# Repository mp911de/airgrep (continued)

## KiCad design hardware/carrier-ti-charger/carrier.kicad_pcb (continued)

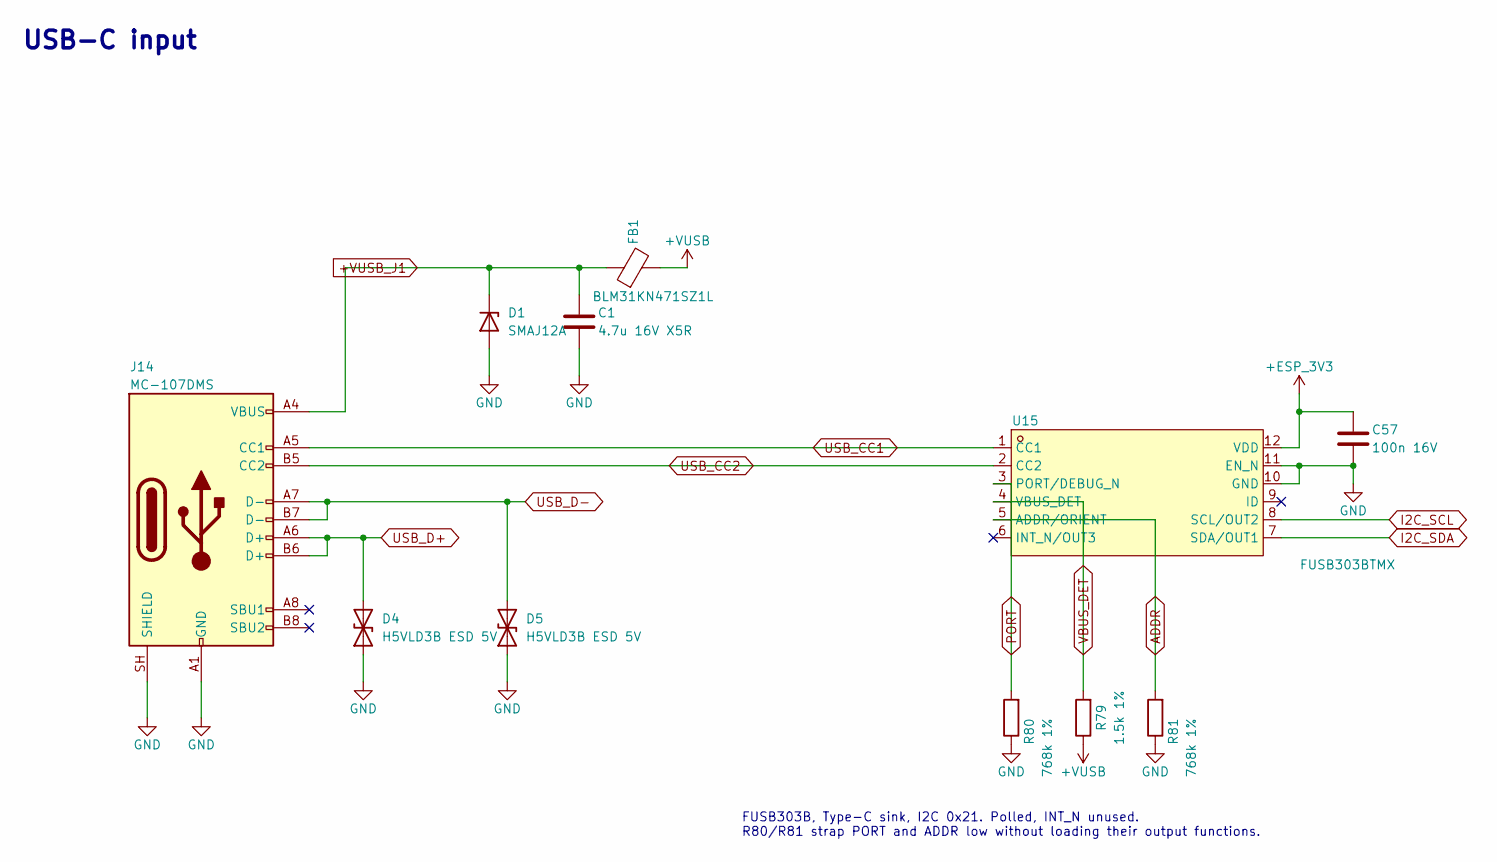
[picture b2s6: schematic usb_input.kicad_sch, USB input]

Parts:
C1: 4.7u 16V X5R; C_0603_1608Metric; LCSC C19666
C57: 100n 16V; C_0402_1005Metric_NoSilk; MPN CL05B104KO5NNNC; LCSC C1525
D1: SMAJ12A; D_SMA; LCSC C19077531
D4, D5: H5VLD3B ESD 5V; D_SOD-323; MPN H5VLD3B; LCSC C20615805
FB1: BLM31KN471SZ1L; L_1206_3216Metric; LCSC C710518
J14: MC-107DMS; USB_C_Receptacle_Hanbo_MC-107DMS; LCSC C3039295
R79: 1.5k 1%; R_0402_1005Metric_NoSilk; MPN 0402WGF1501TCE; LCSC C25867
R80, R81: 768k 1%; R_0402_1005Metric_NoSilk; MPN FRC0402F7683TS; LCSC C49196905
U15: FUSB303BTMX; X2QFN-12_L1.6-W1.6-P0.40-TL; LCSC C895444

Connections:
+ESP_3V3: C57.1, U15.12 (VDD); also elsewhere on the board
+VUSB: FB1.2, R79.1; also elsewhere on the board
+VUSB_J1: C1.1, D1.1 (K), FB1.1, J14.A4 (VBUS), J14.A9 (VBUS), J14.B4 (VBUS), J14.B9 (VBUS)
ADDR: R81.2, U15.5 (ADDR/ORIENT)
GND: C1.2, C57.2, D1.2 (A), D4.1 (A1), D5.1 (A1), J14.A1 (GND), J14.A12 (GND), J14.B1 (GND), J14.B12 (GND), J14.SH (SHIELD), R80.1, R81.1, U15.10 (GND), U15.11 (EN_N); also elsewhere on the board
I2C_SCL: U15.8 (SCL/OUT2); also elsewhere on the board
I2C_SDA: U15.7 (SDA/OUT1); also elsewhere on the board
PORT: R80.2, U15.3 (PORT/DEBUG_N)
USB_CC1: J14.A5 (CC1), U15.1 (CC1)
USB_CC2: J14.B5 (CC2), U15.2 (CC2)
USB_D+: D4.2 (A2), J14.A6 (D+), J14.B6 (D+); also elsewhere on the board
USB_D-: D5.2 (A2), J14.A7 (D-), J14.B7 (D-); also elsewhere on the board
VBUS_DET: R79.2, U15.4 (VBUS_DET)

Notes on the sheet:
USB-C input
FUSB303B, Type-C sink, I2C 0x21. Polled, INT_N unused. R80/R81 strap PORT and ADDR low without loading their output functions.

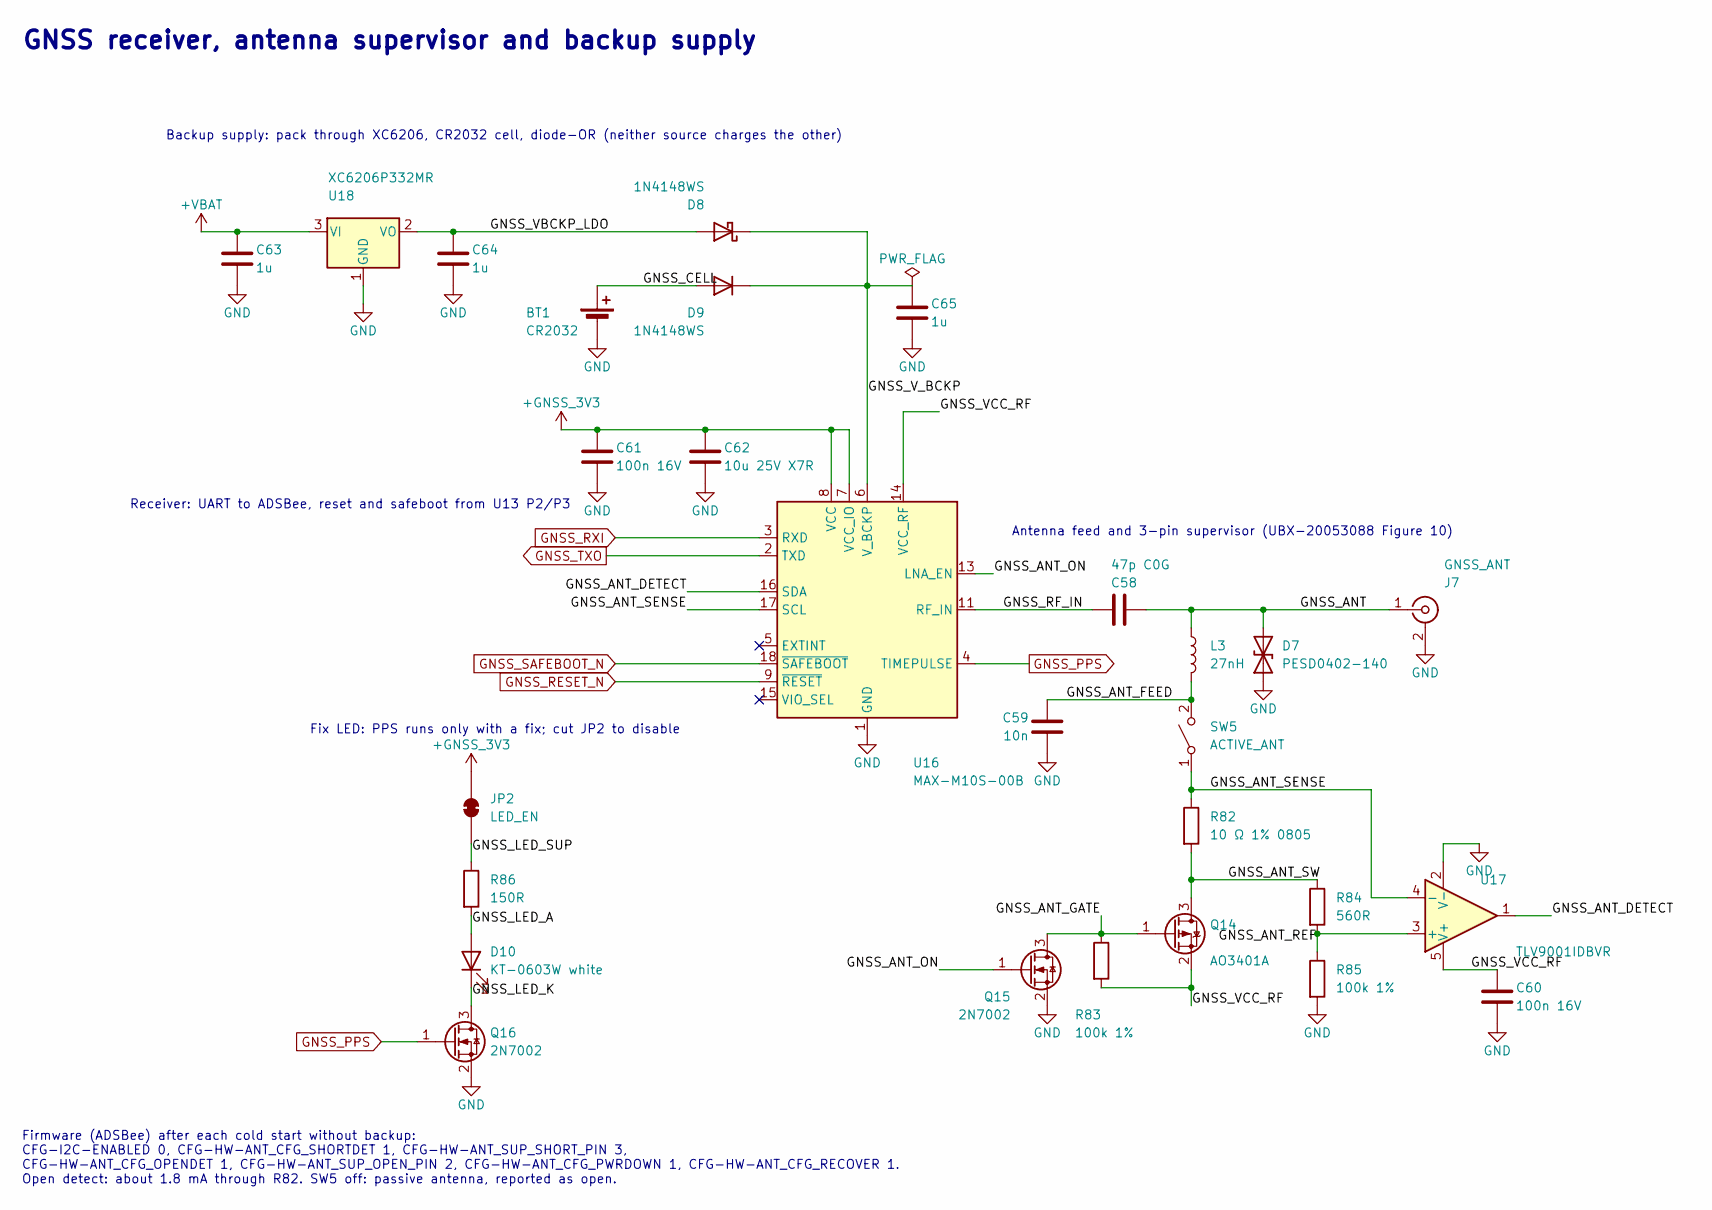
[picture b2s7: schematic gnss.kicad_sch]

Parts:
BT1: CR2032; BAT-SMD_BS-CR2032-8; MPN BS-CR2032-8; LCSC C7498149
C58: 47p C0G; C_0402_1005Metric_NoSilk; MPN 0402CG470J500NT; LCSC C1567
C59: 10n; C_0603_1608Metric; LCSC C57112
C60, C61: 100n 16V; C_0402_1005Metric_NoSilk; MPN CL05B104KO5NNNC; LCSC C1525
C62: 10u 25V X7R; C_0805_2012Metric; MPN CL21B106KAYQNNE; LCSC C3039694
C63, C64, C65: 1u; C_0603_1608Metric; MPN CL10A105KB8NNNC; LCSC C15849
D7: PESD0402-140; D_0402_1005Metric; MPN PESD0402-140; LCSC C10662
D8, D9: 1N4148WS; D_SOD-323; MPN 1N4148WS; LCSC C2128
D10: KT-0603W white; LED_0603_1608Metric; MPN KT-0603W; LCSC C2290
J7: GNSS_ANT; U.FL_Hirose_U.FL-R-SMT-1_Vertical; MPN U.FL-R-SMT-1(80); LCSC C88374
JP2: LED_EN; SolderJumper-2_P1.3mm_Bridged_RoundedPad1.0x1.5mm
L3: 27nH; L_0402_1005Metric; MPN LQG15HS27NJ02D; LCSC C12669
Q14: AO3401A; SOT-23; MPN AO3401A; LCSC C15127
Q15, Q16: 2N7002; SOT-23; MPN 2N7002; LCSC C8545
R82: 10 Ω 1% 0805; R_0805_2012Metric_NoSilk; LCSC C17415
R83, R85: 100k 1%; R_0603_1608Metric; LCSC C25803
R84: 560R; R_0603_1608Metric; MPN 0603WAF5600T5E; LCSC C23204
R86: 150R; R_0603_1608Metric; LCSC C22808
SW5: ACTIVE_ANT; SW-SMD_SHOUHAN_2.54-1P_TPGT; MPN 2.54-1P TPGT; LCSC C7421519
U16: MAX-M10S-00B; ublox_MAX-M10S; MPN MAX-M10S-00B; LCSC C4153167
U17: TLV9001IDBVR; SOT-23-5; MPN TLV9001IDBVR; LCSC C398363
U18: XC6206P332MR; SOT-23; MPN XC6206P332MR; LCSC C5446

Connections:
+GNSS_3V3: C61.1, C62.1, JP2.2 (B), U16.7 (VCC_IO), U16.8 (VCC); also elsewhere on the board
+VBAT: C63.1, U18.3 (VI); also elsewhere on the board
/GNSS/GNSS_ANT: C58.2, D7.2 (A2), J7.1 (In), L3.1
/GNSS/GNSS_ANT_DETECT: U16.16 (SDA), U17.1
/GNSS/GNSS_ANT_FEED: C59.1, L3.2, SW5.2 (B)
/GNSS/GNSS_ANT_GATE: Q14.1 (G), Q15.3 (D), R83.1
/GNSS/GNSS_ANT_ON: Q15.1 (G), U16.13 (LNA_EN)
/GNSS/GNSS_ANT_REF: R84.2, R85.1, U17.3 (+)
/GNSS/GNSS_ANT_SENSE: R82.1, SW5.1 (A), U16.17 (SCL), U17.4 (-)
/GNSS/GNSS_ANT_SW: Q14.3 (D), R82.2, R84.1
/GNSS/GNSS_CELL: BT1.1 (+), D9.2 (A)
/GNSS/GNSS_LED_A: D10.2 (A), R86.2
/GNSS/GNSS_LED_K: D10.1 (K), Q16.3 (D)
/GNSS/GNSS_LED_SUP: JP2.1 (A), R86.1
/GNSS/GNSS_RF_IN: C58.1, U16.11 (RF_IN)
/GNSS/GNSS_VBCKP_LDO: C64.1, D8.2 (A), U18.2 (VO)
/GNSS/GNSS_VCC_RF: C60.1, Q14.2 (S), R83.2, U16.14 (VCC_RF), U17.5 (V+)
/GNSS/GNSS_V_BCKP: C65.1, D8.1 (K), D9.1 (K), U16.6 (V_BCKP)
GND: BT1.2 (-), C59.2, C60.2, C61.2, C62.2, C63.2, C64.2, C65.2, D7.1 (A1), J7.2 (Ext), Q15.2 (S), Q16.2 (S), R85.2, U16.1 (GND), U16.10 (GND), U16.12 (GND), U17.2 (V-), U18.1 (GND); also elsewhere on the board
GNSS_PPS: Q16.1 (G), U16.4 (TIMEPULSE); also elsewhere on the board
GNSS_RESET_N: U16.9 (~RESET); also elsewhere on the board
GNSS_RXI: U16.3 (RXD); also elsewhere on the board
GNSS_SAFEBOOT_N: U16.18 (~SAFEBOOT); also elsewhere on the board
GNSS_TXO: U16.2 (TXD); also elsewhere on the board

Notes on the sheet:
Antenna feed and 3-pin supervisor (UBX-20053088 Figure 10)
Backup supply: pack through XC6206, CR2032 cell, diode-OR (neither source charges the other)
GNSS receiver, antenna supervisor and backup supply
Fix LED: PPS runs only with a fix; cut JP2 to disable
Firmware (ADSBee) after each cold start without backup: CFG-I2C-ENABLED 0, CFG-HW-ANT_CFG_SHORTDET 1, CFG-HW-ANT_SUP_SHORT_PIN 3, CFG-HW-ANT_CFG_OPENDET 1, CFG-HW-ANT_SUP_OPEN_PIN 2, CFG-HW-ANT_CFG_PWRDOWN 1, CFG-HW-ANT_CFG_RECOVER 1. Open detect: about 1.8 mA through R82. SW5 off: passive antenna,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
Receiver: UART to ADSBee, reset and safeboot from U13 P2/P3

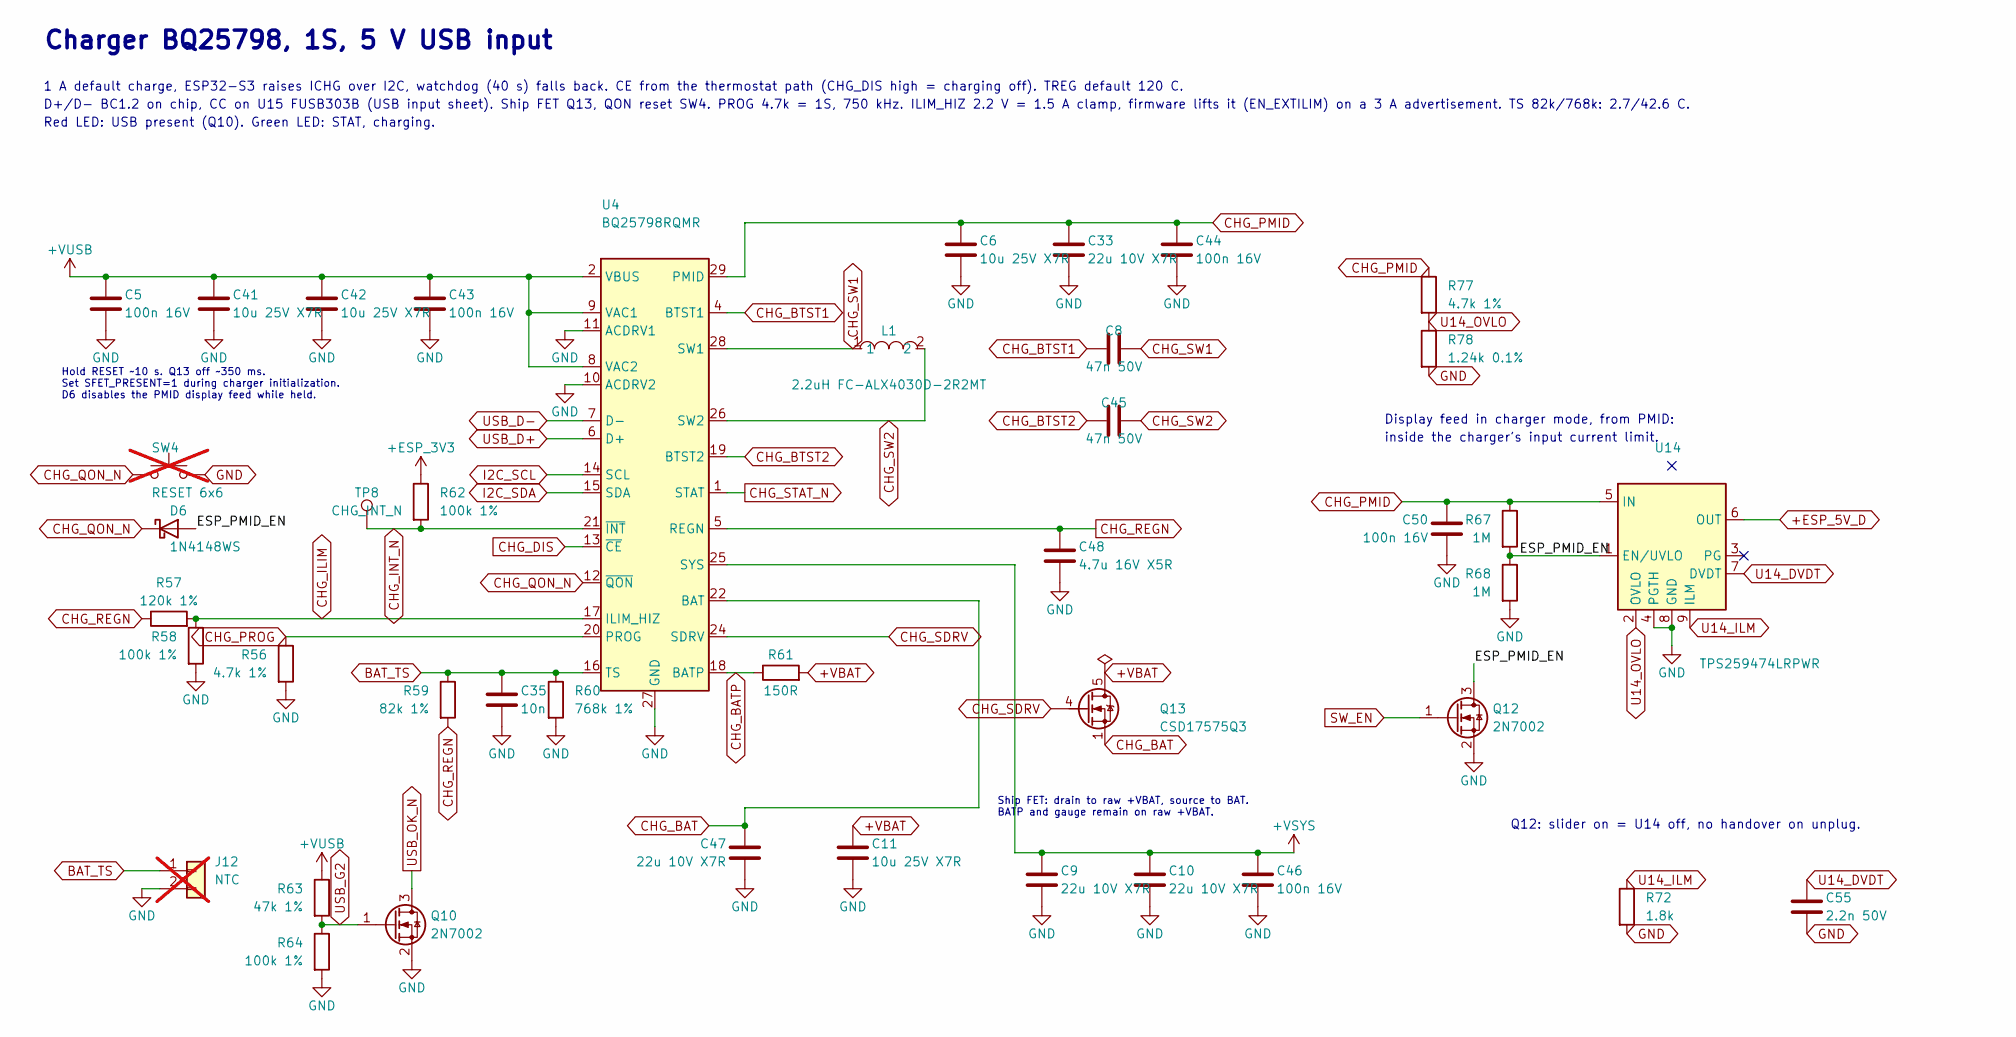
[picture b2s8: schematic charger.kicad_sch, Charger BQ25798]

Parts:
C5, C43, C44, C46, C50: 100n 16V; C_0402_1005Metric_NoSilk; MPN CL05B104KO5NNNC; LCSC C1525
C6, C11, C41, C42: 10u 25V X7R; C_0805_2012Metric; LCSC C3039694
C8, C45: 47n 50V; C_0603_1608Metric; LCSC C1622
C9, C10, C33, C47: 22u 10V X7R; C_0805_2012Metric; LCSC C907991
C35: 10n; C_0603_1608Metric; LCSC C57112
C48: 4.7u 16V X5R; C_0603_1608Metric; LCSC C19666
C55: 2.2n 50V; C_0603_1608Metric; MPN 0603B222K500NT; LCSC C1604
D6: 1N4148WS; D_SOD-323; MPN 1N4148WS; LCSC C2128
J12: NTC; JST_PH_B2B-PH-K_1x02_P2.00mm_Vertical_R10; not fitted
L1: 2.2uH FC-ALX4030D-2R2MT; IND-SMD_L4.2-W4.2_FC-ALX4030D; LCSC C5370906
Q10, Q12: 2N7002; SOT-23; LCSC C8545
Q13: CSD17575Q3; VSON-8_3.3x3.3mm_CSD17575Q3; LCSC C529277
R56: 4.7k 1%; R_0402_1005Metric_NoSilk; MPN 0402WGF4701TCE; LCSC C25900
R57: 120k 1%; R_0603_1608Metric; LCSC C25808
R58, R62, R64: 100k 1%; R_0603_1608Metric; LCSC C25803
R59: 82k 1%; R_0603_1608Metric; Tolerance 1%; MPN 0603WAF8202T5E; LCSC C23254
R60: 768k 1%; R_0402_1005Metric_NoSilk; MPN FRC0402F7683TS; LCSC C49196905
R61: 150R; R_0603_1608Metric; LCSC C22808
R63: 47k 1%; R_0603_1608Metric; LCSC C25819
R67, R68: 1M; R_0603_1608Metric; LCSC C22935
R72: 1.8k; R_0603_1608Metric; Tolerance 1%; MPN 0603WAF1801T5E; LCSC C4177
R77: 4.7k 1%; R_0402_1005Metric_NoSilk; Tolerance 1%; MPN 0402WGF4701TCE; LCSC C25900
R78: 1.24k 0.1%; R_0402_1005Metric_NoSilk; Tolerance 0.1%; MPN ARG02BTC1241; LCSC C2984409
SW4: RESET 6x6; SW_PUSH_6mm; not fitted
TP8: CHG_INT_N; TestPoint_Pad_D1.5mm
U4: BQ25798RQMR; Texas_RQM0029A_VQFN-29_4x4mm_P0.4mm; LCSC C2876593
U14: TPS259474LRPWR; VQFN-10_L2.0-W2.0-P0.45-HR_LM73100; LCSC C2864845

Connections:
+ESP_3V3: R62.1; also elsewhere on the board
+ESP_5V_D: U14.6 (OUT); also elsewhere on the board
+VBAT: C11.1, Q13.5 (D), R61.2; also elsewhere on the board
+VSYS: C9.1, C10.1, C46.1, U4.25 (SYS); also elsewhere on the board
+VUSB: C5.1, C41.1, C42.1, C43.1, R63.1, U4.2 (VBUS), U4.3 (VBUS), U4.8 (VAC2), U4.9 (VAC1); also elsewhere on the board
/Charger BQ25798/ESP_PMID_EN: D6.2 (A), Q12.3 (D), R67.2, R68.1, U14.1 (EN/UVLO)
BAT_TS: C35.1, J12.1, R59.1, R60.1, U4.16 (TS)
CHG_BAT: C47.1, Q13.1 (S), Q13.2 (S), Q13.3 (S), U4.22 (BAT), U4.23 (BAT)
CHG_BATP: R61.1, U4.18 (BATP)
CHG_BTST1: C8.1, U4.4 (BTST1)
CHG_BTST2: C45.1, U4.19 (BTST2)
CHG_DIS: U4.13 (~CE); also elsewhere on the board
CHG_ILIM: R57.2, R58.1, U4.17 (ILIM_HIZ)
CHG_INT_N: R62.2, TP8.1 (1_1), U4.21 (~INT)
CHG_PMID: C6.1, C33.1, C44.1, C50.1, R67.1, R77.1, U4.29 (PMID), U14.5 (IN)
CHG_PROG: R56.1, U4.20 (PROG)
CHG_QON_N: D6.1 (K), SW4.1, U4.12 (~QON)
CHG_REGN: C48.1, R57.1, R59.2, U4.5 (REGN)
CHG_SDRV: Q13.4 (G), U4.24 (SDRV)
CHG_STAT_N: U4.1 (STAT); also elsewhere on the board
CHG_SW1: C8.2, L1.1, U4.28 (SW1)
CHG_SW2: C45.2, L1.2, U4.26 (SW2)
GND: C5.2, C6.2, C9.2, C10.2, C11.2, C33.2, C35.2, C41.2, C42.2, C43.2, C44.2, C46.2, C47.2, C48.2, C50.2, C55.2, J12.2, Q10.2 (S), Q12.2 (S), R56.2, R58.2, R60.2, R64.2, R68.2, R72.2, R78.2, SW4.2, U4.10 (ACDRV2), U4.11 (ACDRV1), U4.27 (GND), U14.4 (PGTH), U14.8 (GND); also elsewhere on the board
I2C_SCL: U4.14 (SCL); also elsewhere on the board
I2C_SDA: U4.15 (SDA); also elsewhere on the board
SW_EN: Q12.1 (G); also elsewhere on the board
U14_DVDT: C55.1, U14.7 (DVDT)
U14_ILM: R72.1, U14.9 (ILM)
U14_OVLO: R77.2, R78.1, U14.2 (OVLO)
USB_D+: U4.6 (D+); also elsewhere on the board
USB_D-: U4.7 (D-); also elsewhere on the board
USB_G2: Q10.1 (G), R63.2, R64.1
USB_OK_N: Q10.3 (D); also elsewhere on the board

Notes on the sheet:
Hold RESET ~10 s. Q13 off ~350 ms. Set SFET_PRESENT=1 during charger initialization. D6 disables the PMID display feed while held.
Ship FET: drain to raw +VBAT, source to BAT. BATP and gauge remain on raw +VBAT.
Display feed in charger mode, from PMID:
1 A default charge, ESP32-S3 raises ICHG over I2C, watchdog (40 s) falls back. CE from the thermostat path (CHG_DIS high = charging off). TREG default 120 C.
inside the charger's input current limit.
Charger BQ25798, 1S, 5 V USB input
D+/D- BC1.2 on chip, CC on U15 FUSB303B (USB input sheet). Ship FET Q13, QON reset SW4. PROG 4.7k = 1S, 750 kHz. ILIM_HIZ 2.2 V = 1.5 A clamp, firmware lifts it (EN_EXTILIM) on a 3 A advertisement. TS 82k/768k: 2.7/42.6 C.
Q12: slider on = U14 off, no handover on unplug.
Red LED: USB present (Q10). Green LED: STAT, charging.

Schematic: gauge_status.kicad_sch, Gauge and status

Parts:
C27: 100n 16V; C_0402_1005Metric_NoSilk; MPN CL05B104KO5NNNC; LCSC C1525
D2: L-115WEGW red/green CC; LED_D3.0mm-3; not fitted
D3: LED 3mm green; LED_D3.0mm; not fitted
Q3, Q4: AO3401A; SOT-23; LCSC C15127
R19, R20: 1.5k; R_0603_1608Metric; Tolerance 1%; MPN 0603WAF1501T5E; LCSC C22843
R23, R26, R31: 470R; R_0603_1608Metric; LCSC C23179
R33: 47k 1%; R_0603_1608Metric; LCSC C25819
R36: 100k 1%; R_0603_1608Metric; LCSC C25803
R90, R91: 5.1k; R_0805_2012Metric_Pad1.20x1.40mm_HandSolder; not fitted
U8: MAX17048G+T10; TDFN-8_L2.0-W2.0-P0.50-EP0.8x1.38_T822; LCSC C2682616

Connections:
+5V: R26.1; also elsewhere on the board
+ESP_3V3: R19.1, R20.1, R90.1, R91.1; also elsewhere on the board
+VBAT: C27.1, U8.2 (CELL), U8.3 (VDD); also elsewhere on the board
+VSYS: Q3.2 (S), Q4.2 (S), R33.1, R36.1; also elsewhere on the board
CHG_STAT_N: Q3.1 (G), R33.2; also elsewhere on the board
GND: C27.2, D2.2 (K), D3.1 (K), U8.1 (CTG), U8.4 (GND), U8.6 (QSTRT), U8.9 (EP); also elsewhere on the board
I2C_SCL: R20.2, R91.2, U8.7 (SCL); also elsewhere on the board
I2C_SDA: R19.2, R90.2, U8.8 (SDA); also elsewhere on the board
LED_CHG_A: D2.1 (A1), R23.2
LED_FULL_A: D2.3 (A2), R31.2
LED_G_A: D3.2 (A), R26.2
LED_G_SW: Q3.3 (D), R31.1
LED_R_SW: Q4.3 (D), R23.1
USB_OK_N: Q4.1 (G), R36.2; also elsewhere on the board

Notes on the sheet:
Fuel gauge
Status LEDs
Fuel gauge (MAX17048) and status LEDs

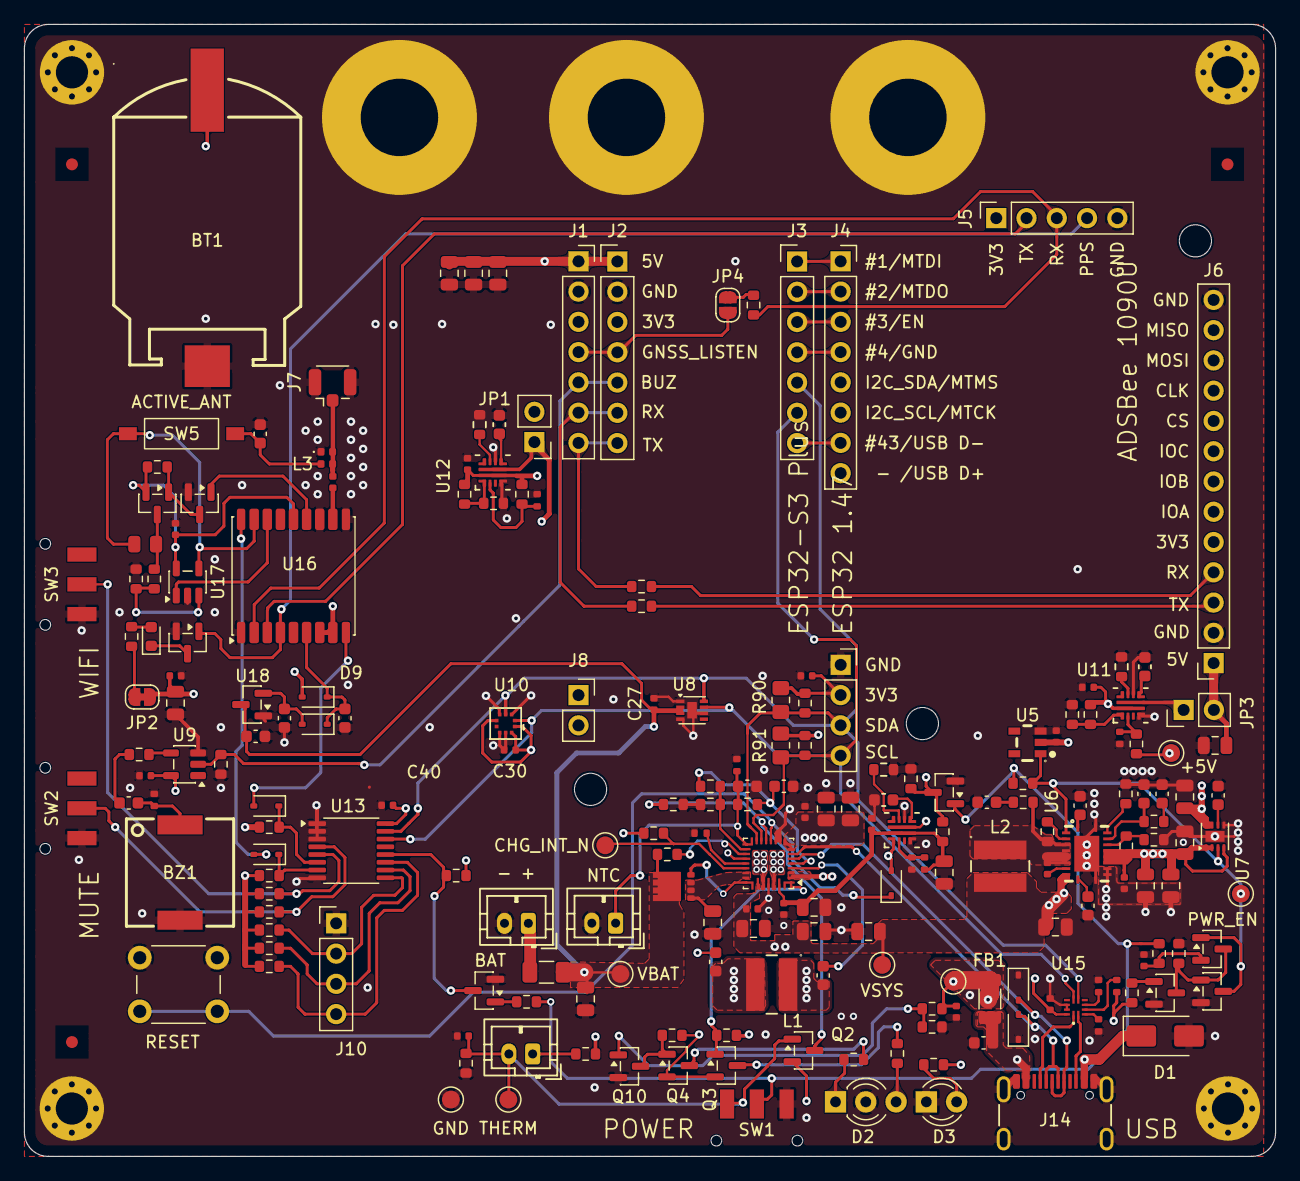
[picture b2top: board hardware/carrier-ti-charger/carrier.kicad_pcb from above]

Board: 4 copper layers, 105.0 x 95.0 mm, 219 parts (0 on the bottom side), 121 nets.

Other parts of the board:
FID1, FID2, FID3: Fiducial; Fiducial_1mm_Mask2mm
MH1, MH2, MH3, MH4: MountingHole_2.7mm_M2.5_Pad_Via
MH6ANTGNSS, MH7ADS1090, MH8ADS980: MountingHole_6.5mm_Pad
MH12, MH13, MH14: MountingHole_2.7mm_M2.5

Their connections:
GND: MH1.1, MH2.1, MH3.1, MH4.1, MH6ANTGNSS.1, MH7ADS1090.1, MH8ADS980.1; also elsewhere on the board

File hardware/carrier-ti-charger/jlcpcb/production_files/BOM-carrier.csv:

Comment,Designator,Footprint,LCSC,Quantity
1.24k 0.1%,R78,R_0402_1005Metric_NoSilk,C2984409,1
1.5k,"R19,R20",R_0603_1608Metric,C22843,2
1.5k 1%,"R74,R76,R79",R_0402_1005Metric_NoSilk,C25867,3
1.8k,"R70,R71,R72",R_0603_1608Metric,C4177,3
10 Ω 1% 0805,R82,R_0805_2012Metric_NoSilk,C17415,1
100k 1%,"R12,R13,R27,R36,R41,R48,R49,R52,R53,R54,R55,R58,R62,R64,R69,R83,R85,R88,R89",R_0603_1608Metric,C25803,19
100n 16V,"C12,C16,C27,C28,C29,C30,C31,C37,C38,C39,C40,C43,C44,C46,C5,C50,C53,C57,C60,C61",C_0402_1005Metric_NoSilk,C1525,20
100p,C22,C_0603_1608Metric,C14858,1
10k,R87,R_0402_1005Metric_NoSilk,C25744,1
10k,R40,R_0603_1608Metric,C25804,1
10n,"C21,C23,C35,C59",C_0603_1608Metric,C57112,4
10u 25V X7R,"C11,C24,C25,C26,C41,C42,C6,C62",C_0805_2012Metric,C3039694,8
120k 1%,R57,R_0603_1608Metric,C25808,1
150R,"R61,R86",R_0603_1608Metric,C22808,2
160k,R17,R_0603_1608Metric,C22813,1
1M,"R10,R42,R44,R45,R46,R47,R67,R68",R_0603_1608Metric,C22935,8
1N4148WS,"D11,D12,D6,D8,D9",D_SOD-323,C2128,5
1k,"R28,R29,R30,R32,R43",R_0603_1608Metric,C21190,5
1u,"C63,C64,C65,C66",C_0603_1608Metric,C15849,4
2.2n 50V,"C54,C55,C56",C_0603_1608Metric,C1604,3
2.2uH FC-ALX4030D-2R2MT,"L1,L2",IND-SMD_L4.2-W4.2_FC-ALX4030D,C5370906,2
220k,R16,R_0603_1608Metric,C22961,1
22u 10V X7R,"C10,C13,C14,C18,C19,C20,C33,C47,C51,C52,C9",C_0805_2012Metric,C907991,11
240k 1%,R14,R_0603_1608Metric,C4197,1
27nH,L3,L_0402_1005Metric,C12669,1
2N7002,"Q10,Q11,Q12,Q15,Q16,Q8,Q9",SOT-23,C8545,7
4.7k 1%,"R56,R77",R_0402_1005Metric_NoSilk,C25900,2
4.7u 16V X5R,"C1,C15,C48",C_0603_1608Metric,C19666,3
470R,"R23,R26,R31",R_0603_1608Metric,C23179,3
47k 1%,"R33,R63",R_0603_1608Metric,C25819,2
47n 50V,"C17,C45,C8",C_0603_1608Metric,C1622,3
47p C0G,C58,C_0402_1005Metric_NoSilk,C1567,1
5.6k 1%,"R73,R75",R_0603_1608Metric,C23189,2
560R,R84,R_0603_1608Metric,C23204,1
5A 0466005.NRHF,F1,Fuse_1206_3216Metric,C57525,1
6.8k,R18,R_0603_1608Metric,C23212,1
75k 1%,R15,R_0603_1608Metric,C23242,1
768k 1%,"R60,R80,R81",R_0402_1005Metric_NoSilk,C49196905,3
82k 1%,R59,R_0603_1608Metric,C23254,1
ACTIVE_ANT,SW5,SW-SMD_SHOUHAN_2.54-1P_TPGT,C7421519,1
AO3401A,"Q14,Q2,Q3,Q4,Q7",SOT-23,C15127,5
BLM31KN471SZ1L,FB1,L_1206_3216Metric,C710518,1
BMP580,U10,LGA-10_L2.0-W2.0-P0.50-TL_BMP581,C22391138,1
BQ25798RQMR,U4,Texas_RQM0029A_VQFN-29_4x4mm_P0.4mm,C2876593,1
CR2032,BT1,BAT-SMD_BS-CR2032-8,C7498149,1
CSD17575Q3,Q13,VSON-8_3.3x3.3mm_CSD17575Q3,C529277,1
FUSB303BTMX,U15,X2QFN-12_L1.6-W1.6-P0.40-TL,C895444,1
GNSS_ANT,J7,U.FL_Hirose_U.FL-R-SMT-1_Vertical,C88374,1
H5VLD3B ESD 5V,"D4,D5",D_SOD-323,C20615805,2
K3-1280S-F1,"SW1,SW2,SW3",SW-SMD_K3-1280S-F1,C92658,3
KT-0603W white,D10,LED_0603_1608Metric,C2290,1
MAX-M10S-00B,U16,ublox_MAX-M10S,C4153167,1
MAX17048G+T10,U8,TDFN-8_L2.0-W2.0-P0.50-EP0.8x1.38_T822,C2682616,1
MC-107DMS,J14,USB_C_Receptacle_Hanbo_MC-107DMS,C3039295,1
PESD0402-140,D7,D_0402_1005Metric,C10662,1
PKMCS0909E4000-R1,BZ1,BUZ-SMD_L9.0-W9.0_PKMCS0909E4000-R1,C910763,1
SMAJ12A,D1,D_SMA,C19077531,1
SN74LVC1G17DBVR,U9,SOT-23-5,C7836,1
TCA9534PWR,U13,TSSOP-16_4.4x5mm_P0.65mm,C783615,1
TLV840CADL29DBVR 2.9V,U5,SOT-23-5_L2.9-W1.6-P0.95-LS2.8-BR,C3686404,1
TLV9001IDBVR,U17,SOT-23-5,C398363,1
TPS22975DSGR,U7,Texas_DSG0008A_WSON-8-1EP_2x2mm_P0.5mm_EP0.9x1.6mm,C524777,1
TPS259474LRPWR,"U11,U12,U14",VQFN-10_L2.0-W2.0-P0.45-HR_LM73100,C2864845,3
TPS61088RHLR,U6,VQFN-20_L4.6-W3.6-P0.50-BL,C87357,1
XC6206P332MR,U18,SOT-23,C5446,1

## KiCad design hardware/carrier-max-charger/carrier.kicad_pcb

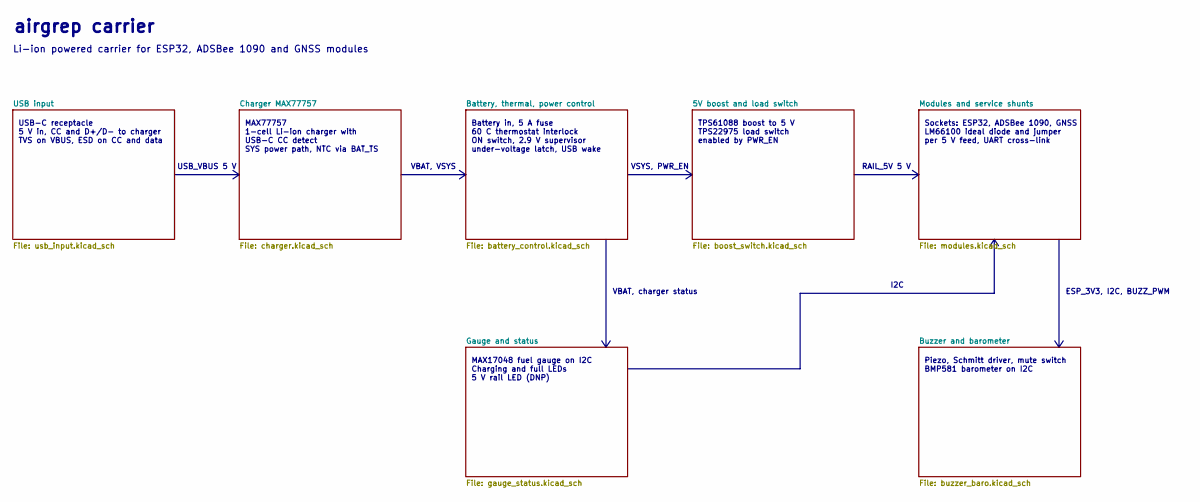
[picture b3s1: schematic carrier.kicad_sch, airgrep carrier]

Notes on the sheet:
I2C
TPS61088 boost to 5 V TPS22975 load switch enabled by PWR_EN
Piezo, Schmitt driver, mute switch BMP581 barometer on I2C
MAX77757 1-cell Li-ion charger with USB-C CC detect SYS power path, NTC via BAT_TS
airgrep carrier
VBAT, VSYS
ESP_3V3, I2C, BUZZ_PWM
VBAT, charger status
Sockets: ESP32, ADSBee 1090, GNSS LM66100 ideal diode and jumper per 5 V feed, UART cross-link
Battery in, 5 A fuse 60 C thermostat interlock ON switch, 2.9 V supervisor under-voltage latch, USB wake
USB_VBUS 5 V
RAIL_5V 5 V
USB-C receptacle 5 V in, CC and D+/D- to charger TVS on VBUS, ESD on CC and data
MAX17048 fuel gauge on I2C Charging and full LEDs 5 V rail LED (DNP)
VSYS, PWR_EN
Li-ion powered carrier for ESP32, ADSBee 1090 and GNSS modules

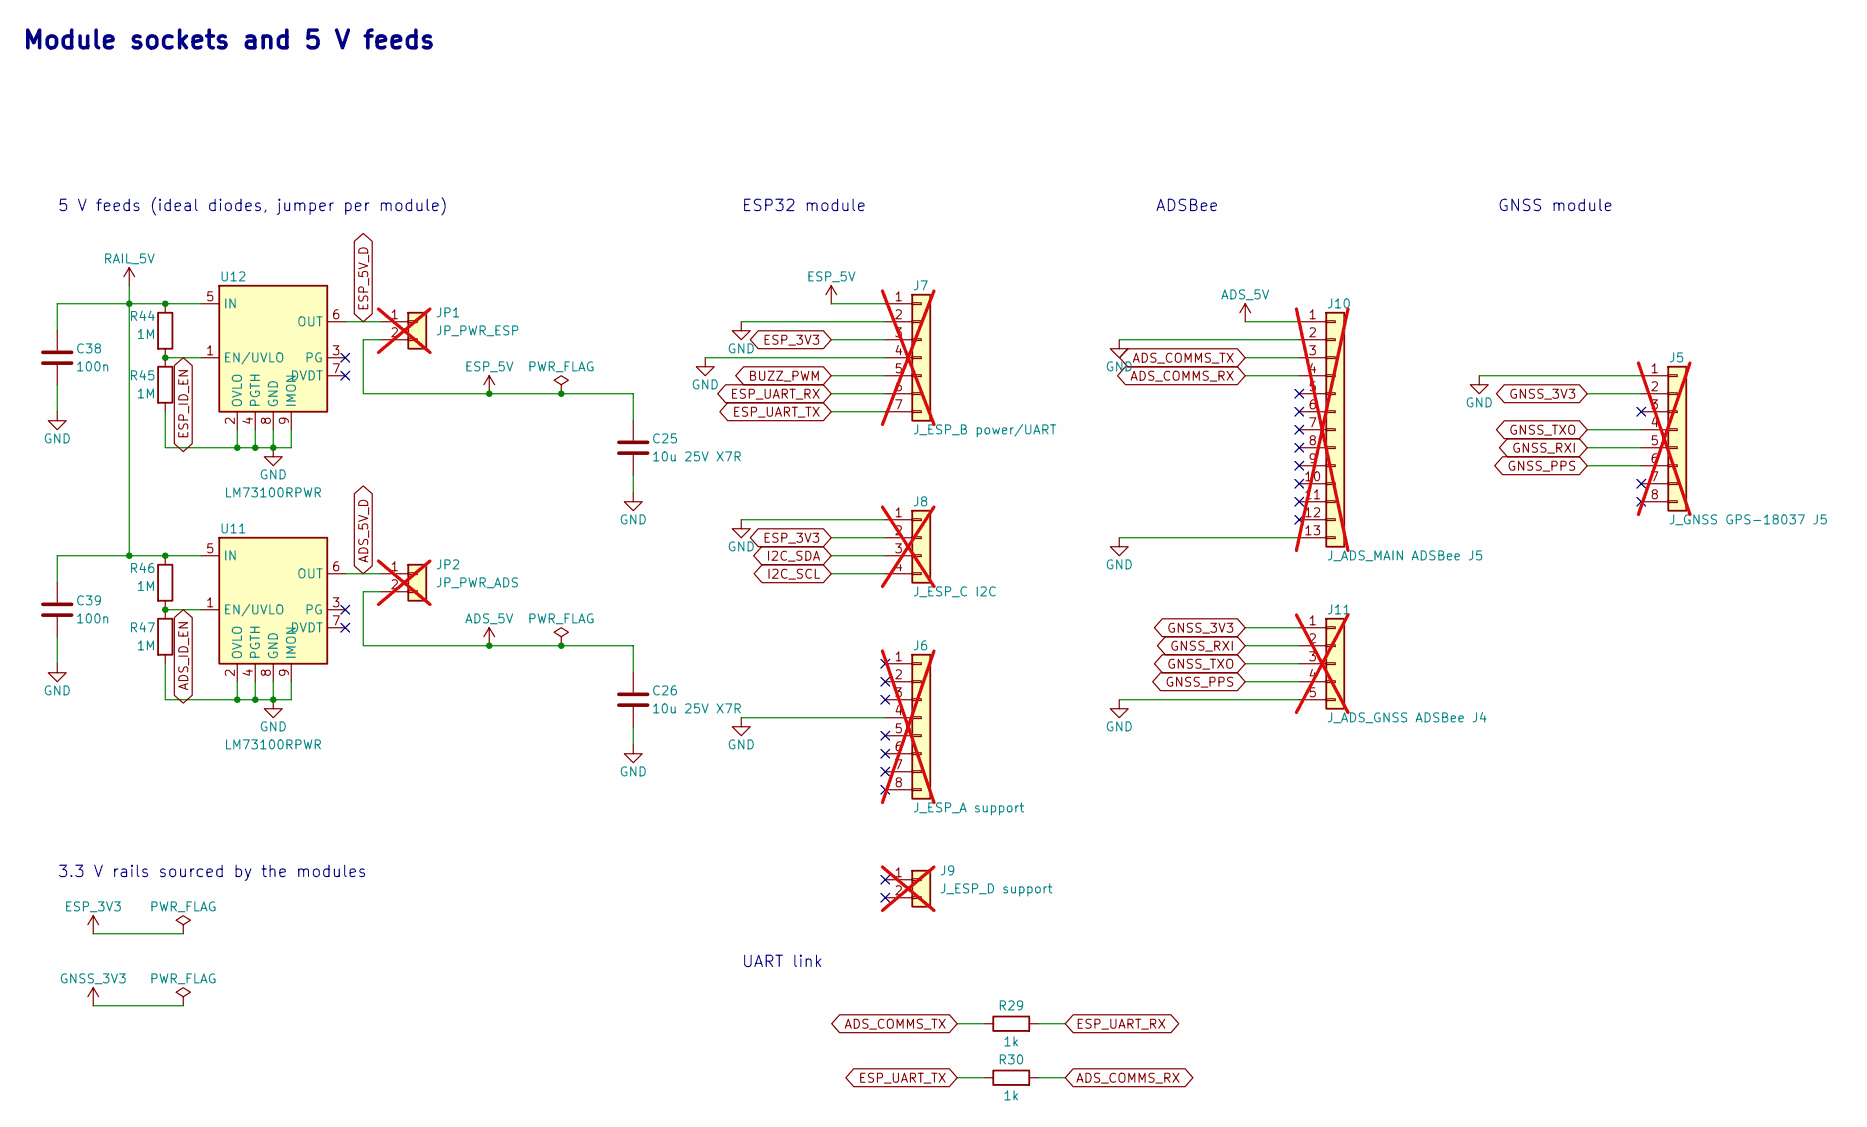
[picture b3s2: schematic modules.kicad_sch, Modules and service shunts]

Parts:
C25, C26: 10u 25V X7R; C_0805_2012Metric; LCSC C3039694
C38, C39: 100n; C_0603_1608Metric; LCSC C14663
J5: J_GNSS GPS-18037 J5; PinSocket_1x08_P2.54mm_Vertical; not fitted
J6: J_ESP_A support; PinSocket_1x08_P2.54mm_Vertical; not fitted
J7: J_ESP_B power/UART; PinSocket_1x07_P2.54mm_Vertical; not fitted
J8: J_ESP_C I2C; PinSocket_1x04_P2.54mm_Vertical; not fitted
J9: J_ESP_D support; PinSocket_1x02_P2.54mm_Vertical; not fitted
J10: J_ADS_MAIN ADSBee J5; PinSocket_1x13_P2.54mm_Vertical; not fitted
J11: J_ADS_GNSS ADSBee J4; PinSocket_1x05_P2.54mm_Vertical; not fitted
JP1: JP_PWR_ESP; PinHeader_1x02_P2.54mm_Vertical; not fitted
JP2: JP_PWR_ADS; PinHeader_1x02_P2.54mm_Vertical; not fitted
R29, R30: 1k; R_0603_1608Metric; LCSC C21190
R44, R45, R46, R47: 1M; R_0603_1608Metric; LCSC C22935
U11, U12: LM73100RPWR; VQFN-10_L2.0-W2.0-P0.45-HR_LM73100; LCSC C3210761

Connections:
ADS_5V: C26.1, J10.1, JP2.2
ADS_5V_D: JP2.1, U11.6 (OUT)
ADS_COMMS_RX: J10.4, R30.2
ADS_COMMS_TX: J10.3, R29.1
ADS_ID_EN: R46.2, R47.1, U11.1 (EN/UVLO)
BUZZ_PWM: J7.5; also elsewhere on the board
ESP_3V3: J7.3, J8.2; also elsewhere on the board
ESP_5V: C25.1, J7.1, JP1.2
ESP_5V_D: JP1.1, U12.6 (OUT)
ESP_ID_EN: R44.2, R45.1, U12.1 (EN/UVLO)
ESP_UART_RX: J7.6, R29.2
ESP_UART_TX: J7.7, R30.1
GND: C25.2, C26.2, C38.2, C39.2, J5.1, J6.4 (Pin_4_4), J7.2, J7.4, J8.1, J10.2, J10.13, J11.5, R45.2, R47.2, U11.2 (OVLO), U11.4 (PGTH), U11.8 (GND), U11.9 (IMON), U12.2 (OVLO), U12.4 (PGTH), U12.8 (GND), U12.9 (IMON); also elsewhere on the board
GNSS_3V3: J5.2, J11.1
GNSS_PPS: J5.6, J11.4
GNSS_RXI: J5.5, J11.2
GNSS_TXO: J5.4, J11.3
I2C_SCL: J8.4; also elsewhere on the board
I2C_SDA: J8.3; also elsewhere on the board
RAIL_5V: C38.1, C39.1, R44.1, R46.1, U11.5 (IN), U12.5 (IN); also elsewhere on the board

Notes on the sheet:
Module sockets and 5 V feeds
UART link
ADSBee
GNSS module
3.3 V rails sourced by the modules
5 V feeds (ideal diodes, jumper per module)
ESP32 module

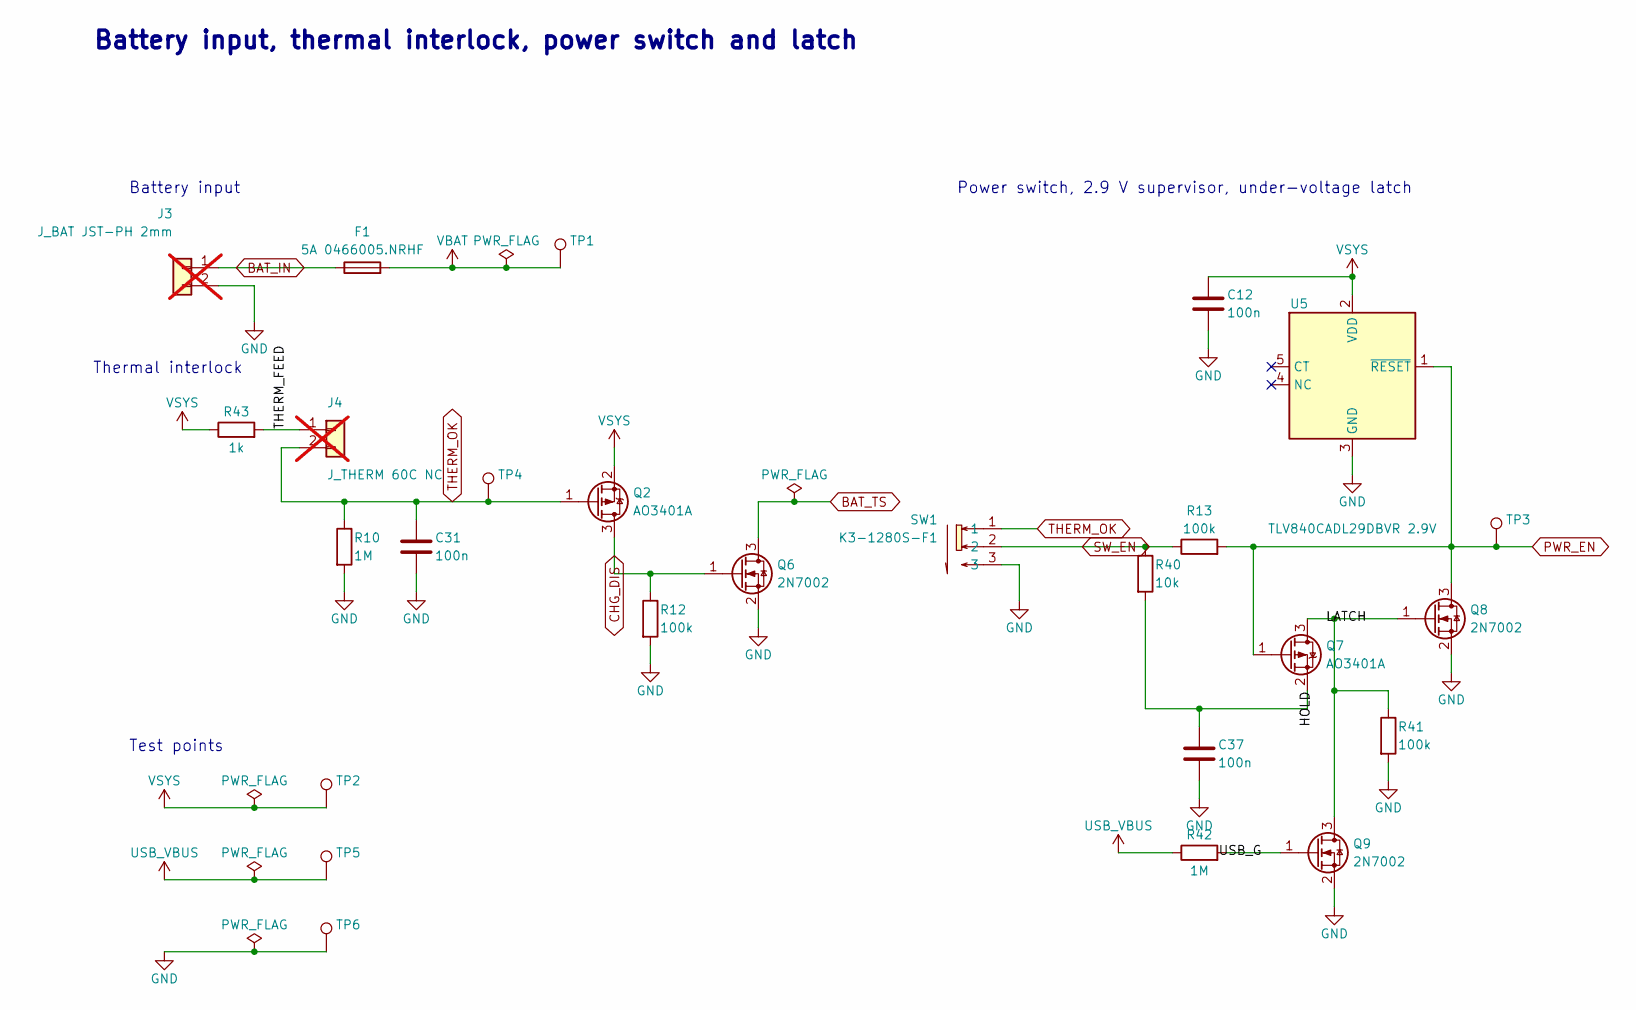
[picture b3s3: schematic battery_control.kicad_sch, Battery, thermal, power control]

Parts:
C12, C31, C37: 100n; C_0603_1608Metric; LCSC C14663
F1: 5A 0466005.NRHF; Fuse_1206_3216Metric; LCSC C57525
J3: J_BAT JST-PH 2mm; JST_PH_B2B-PH-K_1x02_P2.00mm_Vertical_R10; not fitted
J4: J_THERM 60C NC; JST_PH_B2B-PH-K_1x02_P2.00mm_Vertical_R10; not fitted
Q2, Q7: AO3401A; SOT-23; LCSC C15127
Q6, Q8, Q9: 2N7002; SOT-23; LCSC C8545
R10, R42: 1M; R_0603_1608Metric; LCSC C22935
R12, R13, R41: 100k; R_0603_1608Metric; LCSC C25803
R40: 10k; R_0603_1608Metric; LCSC C25804
R43: 1k; R_0603_1608Metric; LCSC C21190
SW1: K3-1280S-F1; SW-SMD_K3-1280S-F1; LCSC C92658
TP1: VBAT; TestPoint_Pad_D1.5mm
TP2: VSYS; TestPoint_Pad_D1.5mm
TP3: PWR_EN; TestPoint_Pad_D1.5mm
TP4: THERM_OK; TestPoint_Pad_D1.5mm
TP5: USB_VBUS; TestPoint_Pad_D1.5mm
TP6: GND; TestPoint_Pad_D1.5mm
U5: TLV840CADL29DBVR 2.9V; SOT-23-5_L2.9-W1.6-P0.95-LS2.8-BR; LCSC C3686404

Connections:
/Battery, thermal, power control/HOLD: C37.2, Q7.2 (S), R40.2
/Battery, thermal, power control/LATCH: Q7.3 (D), Q8.1 (G), Q9.3 (D), R41.1
/Battery, thermal, power control/THERM_FEED: J4.1, R43.2
/Battery, thermal, power control/USB_G: Q9.1 (G), R42.2
BAT_IN: F1.1, J3.1
BAT_TS: Q6.3 (D); also elsewhere on the board
CHG_DIS: Q2.3 (D), Q6.1 (G), R12.1
GND: C12.2, C31.2, C37.1, J3.2, Q6.2 (S), Q8.2 (S), Q9.2 (S), R10.2, R12.2, R41.2, SW1.3, TP6.1 (1_1), U5.3 (GND); also elsewhere on the board
PWR_EN: Q7.1 (G), Q8.3 (D), R13.2, TP3.1 (1_1), U5.1 (~RESET); also elsewhere on the board
SW_EN: R13.1, R40.1, SW1.2
THERM_OK: C31.1, J4.2, Q2.1 (G), R10.1, SW1.1, TP4.1 (1_1)
USB_VBUS: R42.1, TP5.1 (1_1); also elsewhere on the board
VBAT: F1.2, TP1.1 (1_1); also elsewhere on the board
VSYS: C12.1, Q2.2 (S), R43.1, TP2.1 (1_1), U5.2 (VDD); also elsewhere on the board

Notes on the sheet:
Battery input
Battery input, thermal interlock, power switch and latch
Power switch, 2.9 V supervisor, under-voltage latch
Test points
Thermal interlock
